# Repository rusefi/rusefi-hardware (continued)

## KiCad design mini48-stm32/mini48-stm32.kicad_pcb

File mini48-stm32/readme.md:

Brain board stm lqfp48 pin

* TC2030
* CANbus

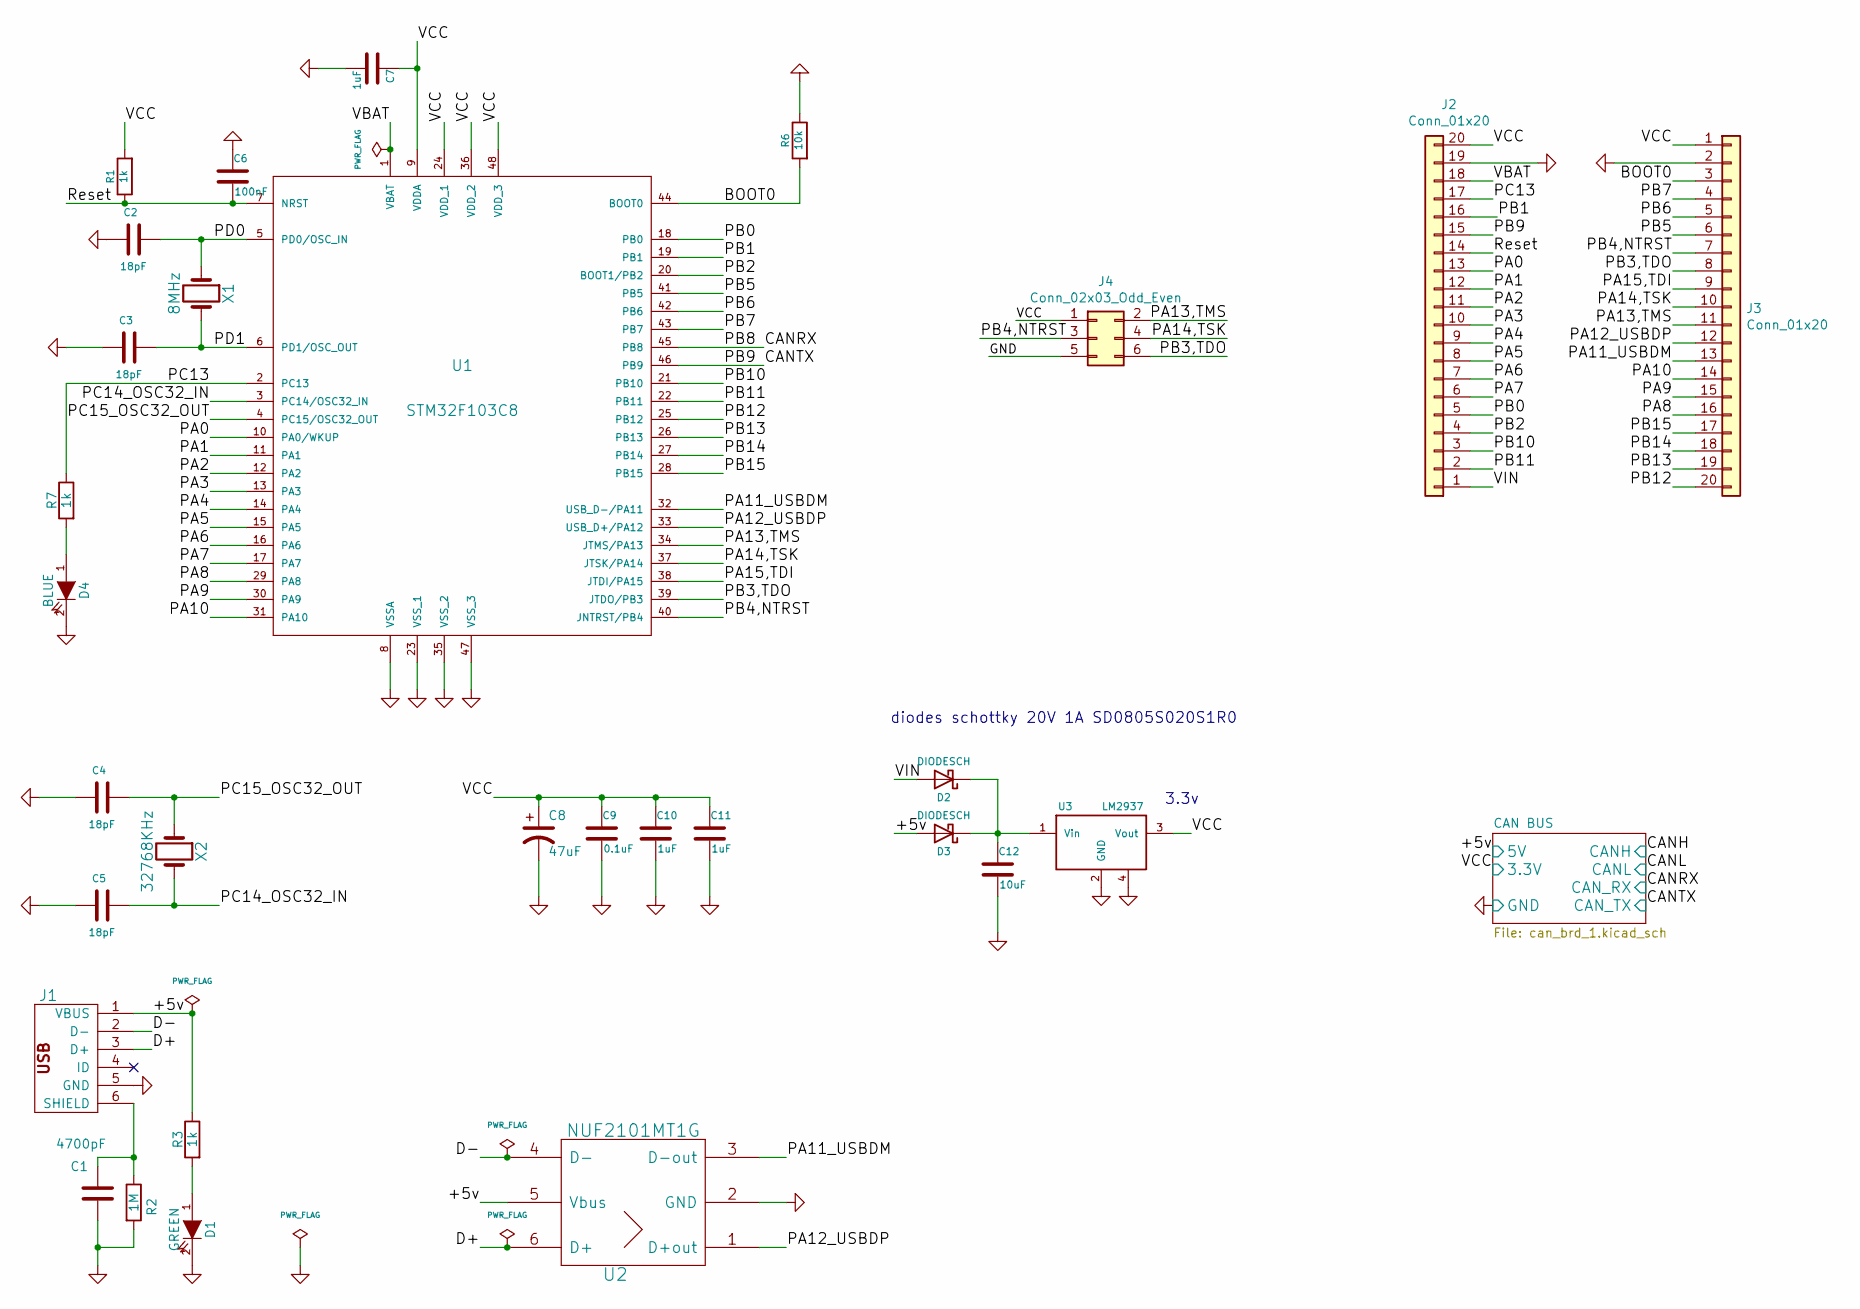
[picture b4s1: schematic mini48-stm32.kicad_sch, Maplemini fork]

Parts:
C1: 4700pF; C_0805_2012Metric; MPN 0805B472K500CT; JLC PN C123621
C2, C3, C4, C5: 18pF; C_0805_2012Metric; MPN CC0805JRNPO9BN180; JLC PN C113825
C6: 100nF; C_0805_2012Metric; MPN CC0805JRX7R9BB104; JLC PN C111492
C7, C10, C11: 1uF; C_0805_2012Metric; MPN CC0805ZKY5V9BB105; JLC PN C106838
C8: 47uF; CP_Elec_4x5.3; MPN GRM21BR61A476ME15L; JLC PN C124129
C9: 0.1uF; C_0805_2012Metric; MPN CC0805JRX7R9BB104; JLC PN C111492
C12: 10uF; C_0805_2012Metric; MPN GRM21BR71A106KA73L; JLC PN C117956
D1: GREEN; LED-0805_A; MPN C693904; JLC PN MHS171UGCT
D2, D3: DIODESCH; D_0805_2012Metric
D4: BLUE; LED-0805_A; MPN C99870; JLC PN 17-21/BHC-AP1Q2/3T
J1: MINI-USB; MINI-USB-5P-3400020P1
J2, J3: Conn_01x20; PIN_ARRAY_20X1
J4: Conn_02x03_Odd_Even; Tag-Connect_TC2030-IDC-NL_2x03_P1.27mm_Vertical
R1, R3, R7: 1k; R_0805_2012Metric; MPN ARG05FTC1001; JLC PN C218388
R2: 1M; R_0805_2012Metric; MPN ERJ6GEYJ105V; JLC PN C230655
R6: 10k; R_0805_2012Metric; MPN RMS10FT1002; JLC PN C212284
U1: STM32F103C8; LQFP-48_7x7mm_P0.5mm; MPN STM32F103C8T6
U2: NUF2101MT1G; SOT-23-6; MPN USBLC6-2SC6; JLC PN C2827654
U3: LM2937; SOT-223; MPN LM2937IMP-3.3/NOPB; JLC PN C140265
X1: 8MHz; HC-49V
X2: 32768KHz; MC-306

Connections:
/+5v: D3.2 (A), J1.1 (VBUS), R3.1, U2.5 (Vbus); also elsewhere on the board
/BOOT0: J3.3, R6.2, U1.44 (BOOT0)
/CANRX: U1.45 (PB8); also elsewhere on the board
/CANTX: J2.15, U1.46 (PB9); also elsewhere on the board
/D+: J1.3 (D+), U2.6 (D+)
/D-: J1.2 (D-), U2.4 (D-)
/PA0: J2.13, U1.10 (PA0/WKUP)
/PA1: J2.12, U1.11 (PA1)
/PA2: J2.11, U1.12 (PA2)
/PA3: J2.10, U1.13 (PA3)
/PA4: J2.9, U1.14 (PA4)
/PA5: J2.8, U1.15 (PA5)
/PA6: J2.7, U1.16 (PA6)
/PA7: J2.6, U1.17 (PA7)
/PA8: J3.16, U1.29 (PA8)
/PA9: J3.15, U1.30 (PA9)
/PA10: J3.14, U1.31 (PA10)
/PA11_USBDM: J3.13, U1.32 (USB_D-/PA11), U2.3 (D-out)
/PA12_USBDP: J3.12, U1.33 (USB_D+/PA12), U2.1 (D+out)
/PA13,TMS: J3.11, J4.2, U1.34 (JTMS/PA13)
/PA14,TSK: J3.10, J4.4, U1.37 (JTSK/PA14)
/PA15,TDI: J3.9, U1.38 (JTDI/PA15)
/PB0: J2.5, U1.18 (PB0)
/PB1: J2.16, U1.19 (PB1)
/PB2: J2.4, U1.20 (BOOT1/PB2)
/PB3,TDO: J3.8, J4.6, U1.39 (JTDO/PB3)
/PB4,NTRST: J3.7, J4.3, U1.40 (JNTRST/PB4)
/PB5: J3.6, U1.41 (PB5)
/PB6: J3.5, U1.42 (PB6)
/PB7: J3.4, U1.43 (PB7)
/PB10: J2.3, U1.21 (PB10)
/PB11: J2.2, U1.22 (PB11)
/PB12: J3.20, U1.25 (PB12)
/PB13: J3.19, U1.26 (PB13)
/PB14: J3.18, U1.27 (PB14)
/PB15: J3.17, U1.28 (PB15)
/PC13: J2.17, R7.1, U1.2 (PC13)
/PC14_OSC32_IN: C5.2, U1.3 (PC14/OSC32_IN), X2.2
/PC15_OSC32_OUT: C4.2, U1.4 (PC15/OSC32_OUT), X2.1
/PD0: C2.2, U1.5 (PD0/OSC_IN), X1.1
/PD1: C3.2, U1.6 (PD1/OSC_OUT), X1.2
/Reset: C6.2, J2.14, R1.1, U1.7 (NRST)
/VBAT: J2.18, U1.1 (VBAT)
/VCC: C7.1, C8.1, C9.1, C10.1, C11.1, J2.20, J3.1, J4.1, R1.2, U1.9 (VDDA), U1.24 (VDD_1), U1.36 (VDD_2), U1.48 (VDD_3), U3.3 (Vout); also elsewhere on the board
/VIN: D2.2 (A), J2.1
GND: C1.1, C2.1, C3.1, C4.1, C5.1, C6.1, C7.2, C8.2, C9.2, C10.2, C11.2, C12.2, D1.2 (K), D4.2 (K), J1.5 (GND), J2.19, J3.2, J4.5, R2.2, R6.1, U1.8 (VSSA), U1.23 (VSS_1), U1.35 (VSS_2), U1.47 (VSS_3), U2.2 (GND), U3.2 (GND), U3.4; also elsewhere on the board
unnamed: C1.2, J1.6 (SHIELD), R2.1
unnamed: C12.1, D2.1 (K), D3.1 (K), U3.1 (Vin)
unnamed: D1.1 (A), R3.2
unnamed: D4.1 (A), R7.2

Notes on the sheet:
diodes schottky 20V 1A SD0805S020S1R0
3.3v

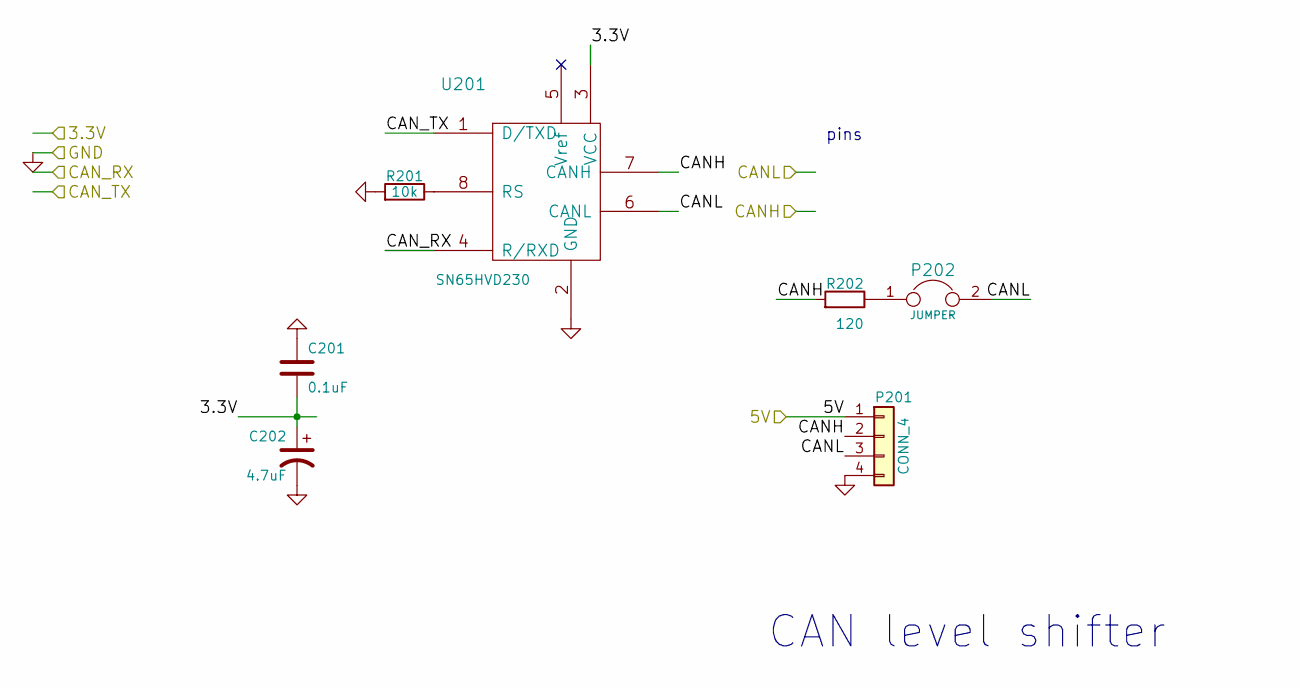
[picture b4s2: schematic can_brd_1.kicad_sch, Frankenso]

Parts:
C201: 0.1uF; C_0805_2012Metric; MPN CC0805JRX7R9BB104; JLC PN C111492
C202: 4.7uF; C_0805_2012Metric; MPN 0805B472K500CT; JLC PN C123621
P201: CONN_4; SIL-4
P202: JUMPER; JUMPER-2
R201: 10k; R_0805_2012Metric; MPN RMS10FT1002; JLC PN C212284
R202: 120; R_0805_2012Metric; MPN CRH0805J120RP05Z; JLC PN C149652
U201: SN65HVD230; SO-8_3.9x4.9mm_P1.27mm; MPN SN65HVD230DR; JLC PN C12084

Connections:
/+5v: P201.1; also elsewhere on the board
/CANH: P201.2, R202.2, U201.7 (CANH)
/CANL: P201.3, P202.2, U201.6 (CANL)
/CANRX: U201.4 (R/RXD); also elsewhere on the board
/CANTX: U201.1 (D/TXD); also elsewhere on the board
/VCC: C201.2, C202.1, U201.3 (VCC); also elsewhere on the board
GND: C201.1, C202.2, P201.4, R201.2, U201.2 (GND); also elsewhere on the board
unnamed: P202.1, R202.1
unnamed: R201.1, U201.8 (RS)

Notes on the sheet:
CAN level shifter
pins

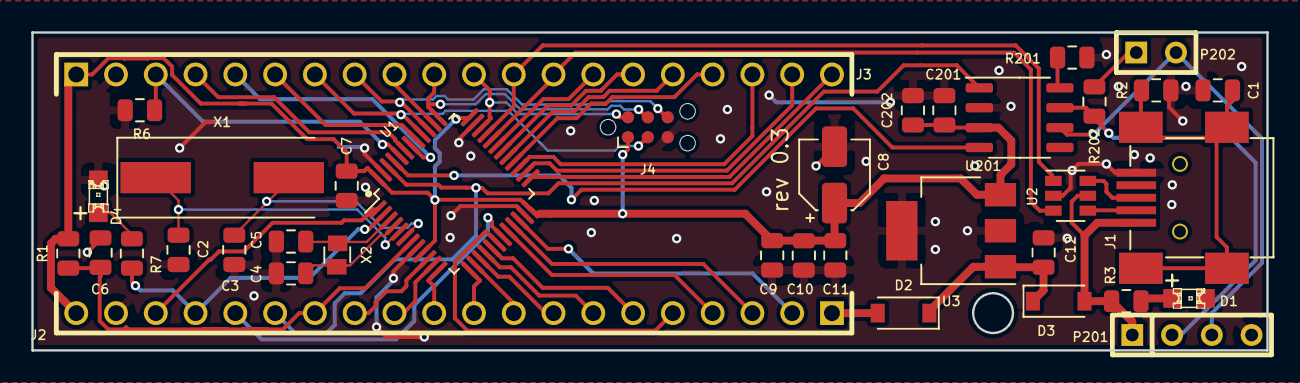
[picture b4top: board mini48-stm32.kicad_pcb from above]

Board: 2 copper layers, 78.9 x 20.3 mm, 37 parts (0 on the bottom side), 54 nets.

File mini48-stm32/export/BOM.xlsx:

Comment | Designator | Footprint | JLCPCB Part #
4700pF | C1 | Capacitor_SMD:C_0805_2012Metric | C123621
18pF | C2 | Capacitor_SMD:C_0805_2012Metric | C113825
18pF | C3 | Capacitor_SMD:C_0805_2012Metric | C113825
12pF | C4 | Capacitor_SMD:C_0805_2012Metric | C0805
12pF | C5 | Capacitor_SMD:C_0805_2012Metric | C0805
100nF | C6 | Capacitor_SMD:C_0805_2012Metric | C111492
1uF | C7 | Capacitor_SMD:C_0805_2012Metric | C106838
47uF | C8 | Capacitor_SMD:CP_Elec_4x5.3 | C124129
0.1uF | C9 | Capacitor_SMD:C_0805_2012Metric | C111492
1uF | C10 | Capacitor_SMD:C_0805_2012Metric | C106838
1uF | C11 | Capacitor_SMD:C_0805_2012Metric | C106838
10uF | C12 | Capacitor_SMD:C_0805_2012Metric | C117956
0.1uF | C201 | Capacitor_SMD:C_0805_2012Metric | C111492
4.7uF | C202 | Capacitor_SMD:C_0805_2012Metric | C123621
GREEN | D1 | LED-0805_A | C693904
DIODESCH | D2 | Diode_SMD:D_SOD-123 | C82288
DIODESCH | D3 | Diode_SMD:D_SOD-123 | C82288
BLUE | D4 | LED-0805_A | C99870
MINI-USB | J1 | MINI-USB-5P-3400020P1 | C2681563
Conn_01x20 | J2 | mini48-stm32:PIN_ARRAY_20X1 | DNP
Conn_01x20 | J3 | mini48-stm32:PIN_ARRAY_20X1 | DNP
Conn_02x03_Odd_Even | J4 | Connector:Tag-Connect_TC2030-IDC-NL_2x03_P1.27mm_Vertical | DNP
CONN_4 | P201 | SIL-4 | DNP
JUMPER | P202 | JUMPER-2 | DNP
1k | R1 | Resistor_SMD:R_0805_2012Metric | C218388
1M | R2 | Resistor_SMD:R_0805_2012Metric | C230655
1k | R3 | Resistor_SMD:R_0805_2012Metric | C218388
10k | R6 | Resistor_SMD:R_0805_2012Metric | C212284
1k | R7 | Resistor_SMD:R_0805_2012Metric | C218388
10k | R201 | Resistor_SMD:R_0805_2012Metric | C212284
120 | R202 | Resistor_SMD:R_0805_2012Metric | C149652
STM32F103C8 | U1 | Package_QFP:LQFP-48_7x7mm_P0.5mm | C8734
NUF2101MT1G | U2 | Package_TO_SOT_SMD:SOT-23-6 | C2827654
LM2937 | U3 | Package_TO_SOT_SMD:SOT-223 | C140265
SN65HVD230 | U201 | Package_SO:SO-8_3.9x4.9mm_P1.27mm | C12084
8MHz | X1 | Crystal:Crystal_SMD_HC49-SD | C106809
32.768KHz | X2 | mini48-stm32:SMD2012-2P | C515343

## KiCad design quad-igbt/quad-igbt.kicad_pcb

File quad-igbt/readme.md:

x4 coil driver

For instance ISL9V3040S3S

See also https://github.com/rusefi/rusefi/tree/master/hardware/DDPAK_breakout

https://www.youtube.com/watch?v=TUJzp6ig_bQ

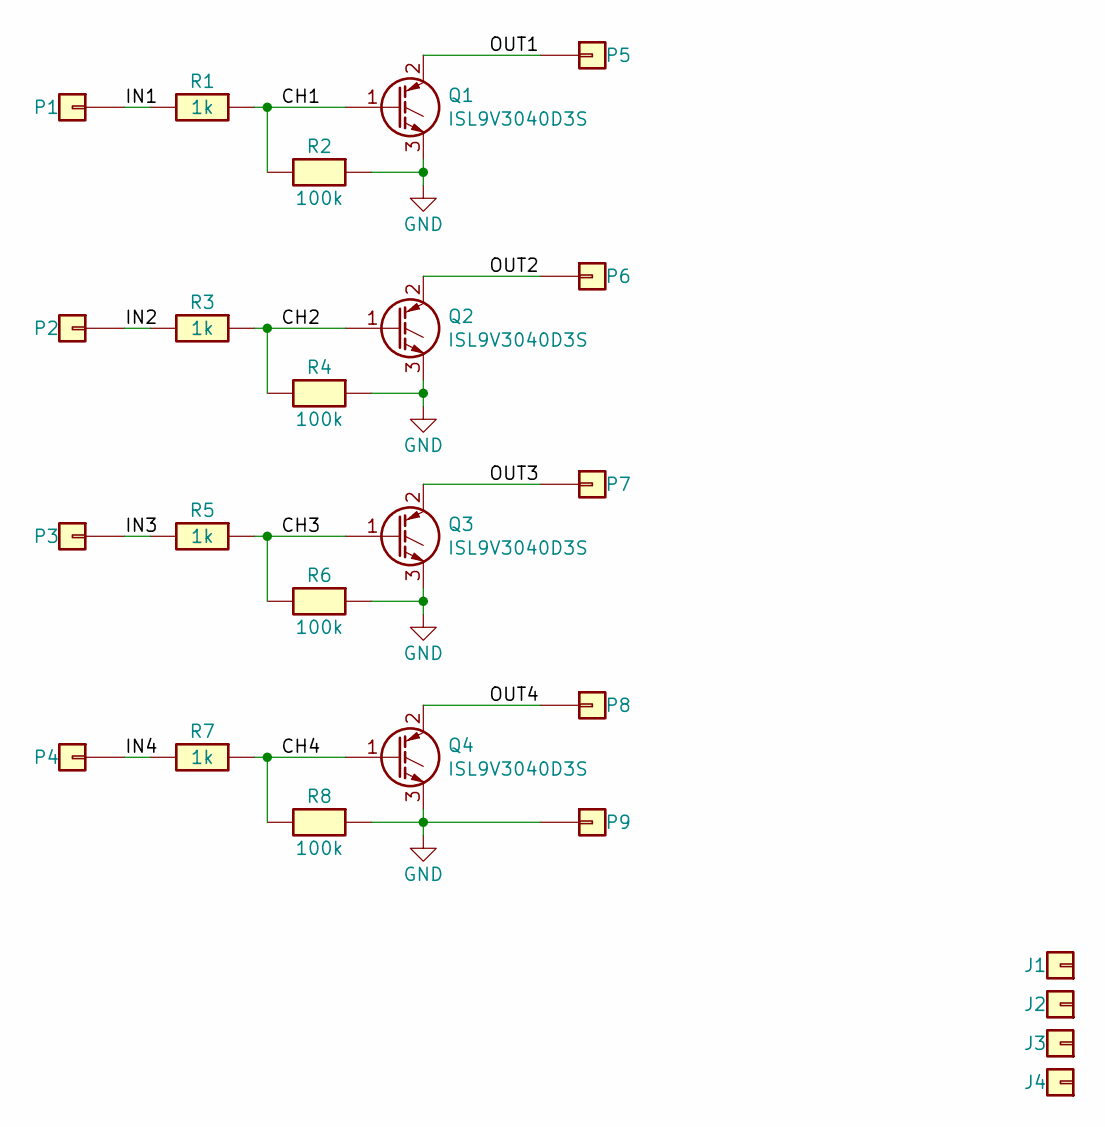
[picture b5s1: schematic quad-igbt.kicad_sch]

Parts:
J1, J2, J3, J4: Conn_01x01; MountingHole_5mm
P1, P2, P3, P4, P5, P6, P7, P8, P9: Pad; PAD-TH
Q1, Q2, Q3, Q4: ISL9V3040D3S; TO-263-2; LCSC C462128
R1, R3, R5, R7: 1k; R0805; LCSC C17513
R2, R4, R6, R8: 100k; R0805; LCSC C149504

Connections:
/CH1: Q1.1 (G), R1.1, R2.2
/CH2: Q2.1 (G), R3.1, R4.2
/CH3: Q3.1 (G), R5.1, R6.2
/CH4: Q4.1 (G), R7.1, R8.2
/IN1: P1.1, R1.2
/IN2: P2.1, R3.2
/IN3: P3.1, R5.2
/IN4: P4.1, R7.2
/OUT1: P5.1, Q1.2 (C)
/OUT2: P6.1, Q2.2 (C)
/OUT3: P7.1, Q3.2 (C)
/OUT4: P8.1, Q4.2 (C)
GND: P9.1, Q1.3 (E), Q2.3 (E), Q3.3 (E), Q4.3 (E), R2.1, R4.1, R6.1, R8.1

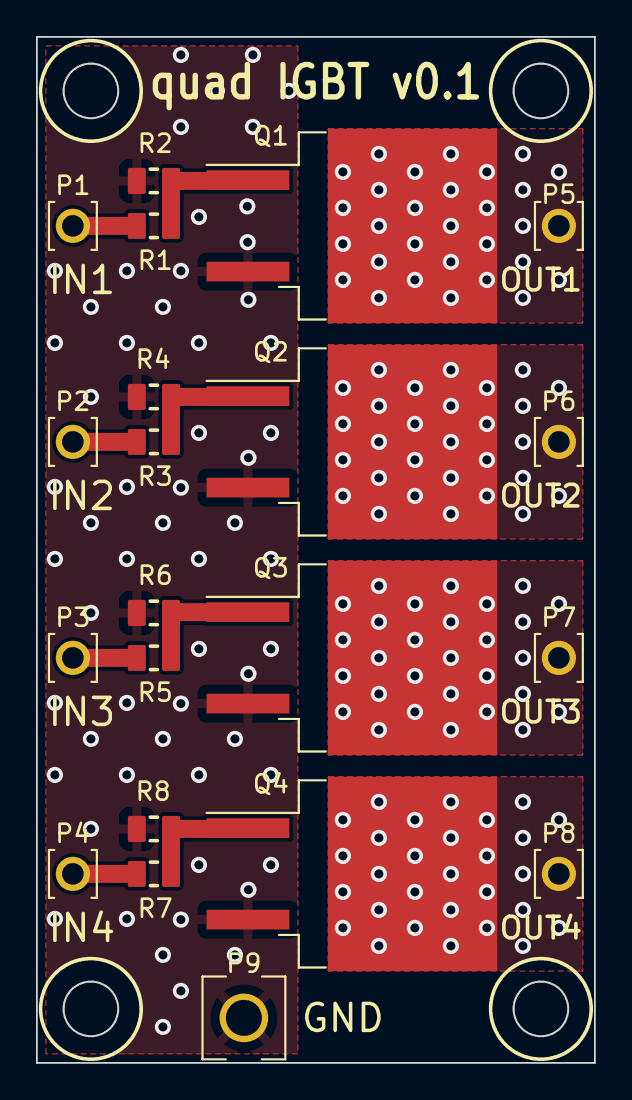
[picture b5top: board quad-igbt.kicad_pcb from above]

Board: 2 copper layers, 31.0 x 57.0 mm, 25 parts (0 on the bottom side), 13 nets.

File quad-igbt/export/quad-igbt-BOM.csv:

Comment,Designator,Footprint,LCSC Part #
"Pad","P1","hellen-one-common:PAD-TH",""
"Pad","P2","hellen-one-common:PAD-TH",""
"Pad","P3","hellen-one-common:PAD-TH",""
"Pad","P4","hellen-one-common:PAD-TH",""
"Pad","P5","hellen-one-common:PAD-TH",""
"Pad","P6","hellen-one-common:PAD-TH",""
"Pad","P7","hellen-one-common:PAD-TH",""
"Pad","P8","hellen-one-common:PAD-TH",""
"Pad","P9","hellen-one-common:PAD-TH",""
"ISL9V3040D3S","Q1","Package_TO_SOT_SMD:TO-263-2","C462128"
"ISL9V3040D3S","Q2","Package_TO_SOT_SMD:TO-263-2","C462128"
"ISL9V3040D3S","Q3","Package_TO_SOT_SMD:TO-263-2","C462128"
"ISL9V3040D3S","Q4","Package_TO_SOT_SMD:TO-263-2","C462128"
"1k","R1","hellen-one-common:R0805","C17513"
"100k","R2","hellen-one-common:R0805","C149504"
"1k","R3","hellen-one-common:R0805","C17513"
"100k","R4","hellen-one-common:R0805","C149504"
"1k","R5","hellen-one-common:R0805","C17513"
"100k","R6","hellen-one-common:R0805","C149504"
"1k","R7","hellen-one-common:R0805","C17513"
"100k","R8","hellen-one-common:R0805","C149504"

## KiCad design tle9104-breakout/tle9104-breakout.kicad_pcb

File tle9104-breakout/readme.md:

See https://github.com/mck1117/tle9104-breakout

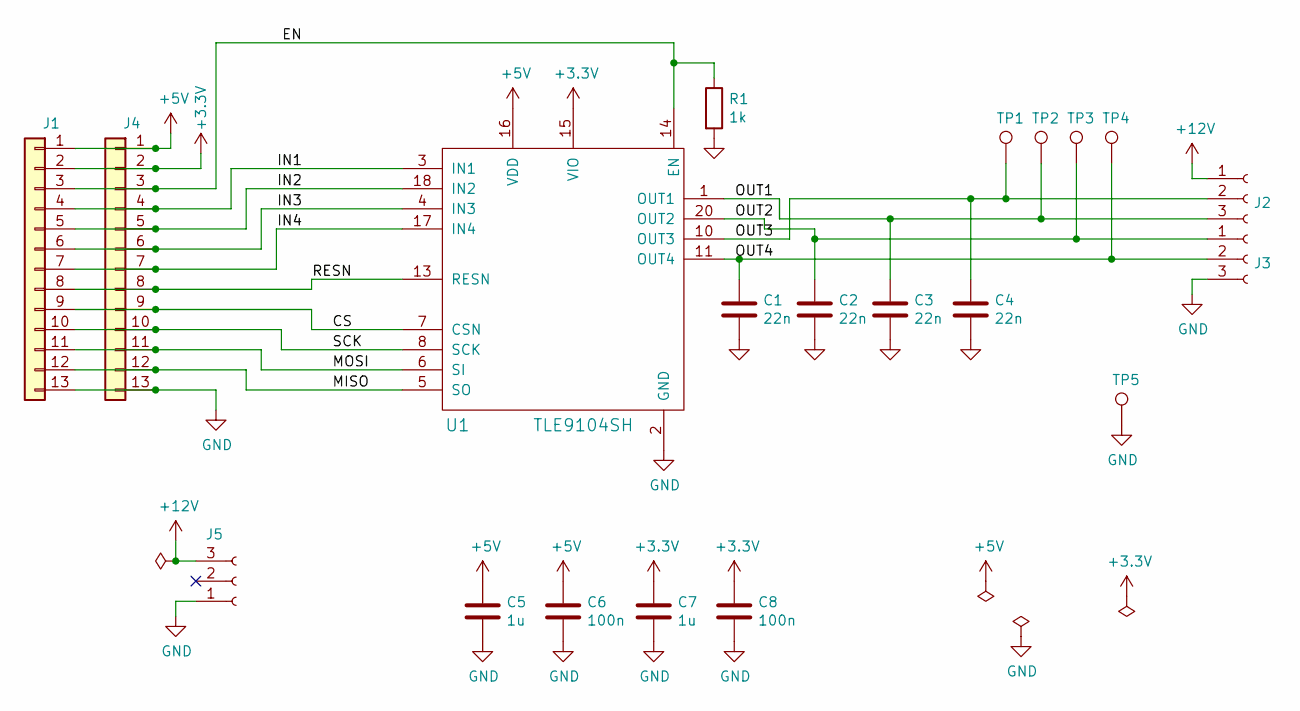
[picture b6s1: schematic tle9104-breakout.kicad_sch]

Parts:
C1, C2, C3, C4: 22n; C_0603_1608Metric; LCSC C21122
C5, C7: 1u; C_0603_1608Metric; LCSC C15849
C6, C8: 100n; C_0402_1005Metric; LCSC C307331
J1, J4: Conn_01x13; PinHeader_1x13_P2.54mm_Vertical
J2, J3: Conn_01x03_Female; PhoenixContact_MCV_1,5_3-G-5.08_1x03_P5.08mm_Vertical
J5: Conn_01x03_Female; PhoenixContact_MSTBVA_2,5_3-G_1x03_P5.00mm_Vertical
R1: 1k; R_0603_1608Metric; LCSC C21190
TP1, TP2, TP3, TP4, TP5: TestPoint; TestPoint_Loop_D2.50mm_Drill1.0mm
U1: TLE9104SH; PG-DSO-20-88; LCSC C2650386

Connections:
+3V3: C7.1, C8.1, J1.2, J4.2, U1.15 (VIO)
+5V: C5.1, C6.1, J1.1, J4.1, U1.16 (VDD)
+12V: J2.1, J5.3
/CS: J1.9, J4.9, U1.7 (CSN)
/EN: J1.3, J4.3, R1.1, U1.14 (EN)
/IN1: J1.4, J4.4, U1.3 (IN1)
/IN2: J1.5, J4.5, U1.18 (IN2)
/IN3: J1.6, J4.6, U1.4 (IN3)
/IN4: J1.7, J4.7, U1.17 (IN4)
/MISO: J1.12, J4.12, U1.5 (SO)
/MOSI: J1.11, J4.11, U1.6 (SI)
/OUT1: C3.1, J2.3, TP2.1, U1.1 (OUT1)
/OUT2: C2.1, J3.1, TP3.1, U1.20 (OUT2)
/OUT3: C4.1, J2.2, TP1.1, U1.10 (OUT3)
/OUT4: C1.1, J3.2, TP4.1, U1.11 (OUT4)
/RESN: J1.8, J4.8, U1.13 (RESN)
/SCK: J1.10, J4.10, U1.8 (SCK)
GND: C1.2, C2.2, C3.2, C4.2, C5.2, C6.2, C7.2, C8.2, J1.13, J3.3, J4.13, J5.1, R1.2, TP5.1, U1.2 (GND), U1.9 (GND), U1.12 (GND), U1.19 (GND), U1.21 (GND)

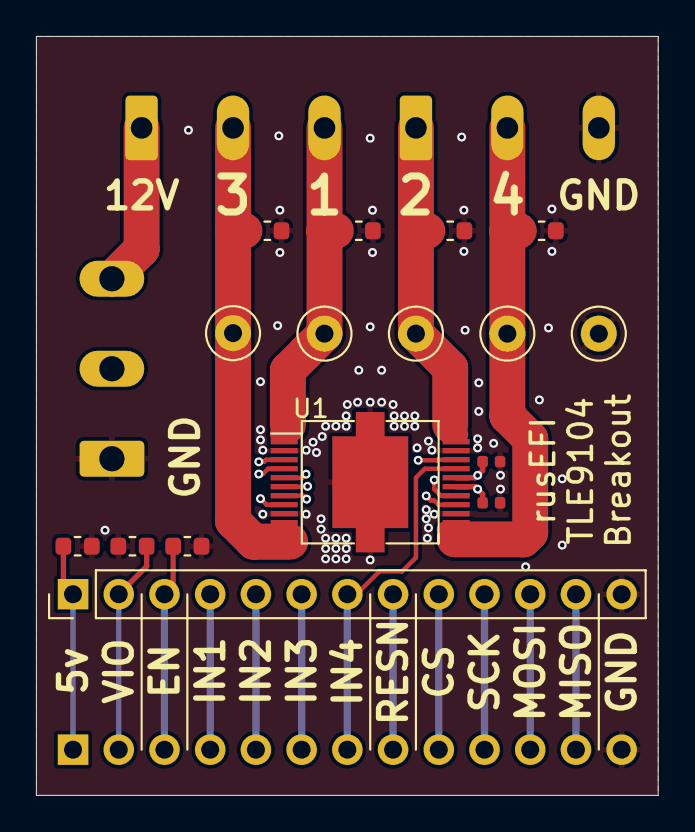
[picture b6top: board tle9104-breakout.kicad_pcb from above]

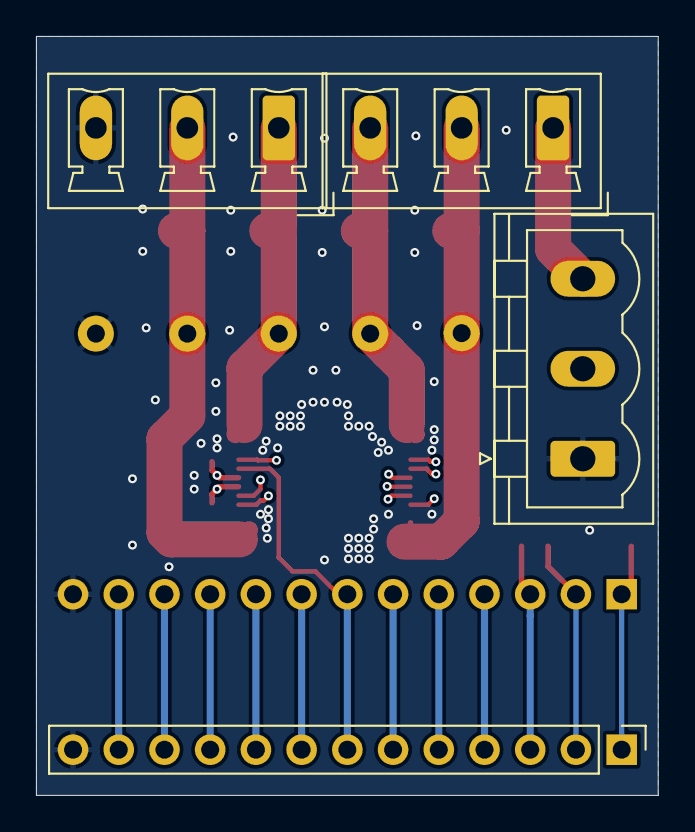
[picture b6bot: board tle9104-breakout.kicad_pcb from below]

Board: 4 copper layers, 34.5 x 42.2 mm, 20 parts (4 on the bottom side), 18 nets.

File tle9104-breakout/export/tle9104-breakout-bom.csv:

"Comment","Designator","Footprint","LCSC Part #"
"22n","C1","Capacitor_SMD:C_0603_1608Metric","C21122"
"22n","C2","Capacitor_SMD:C_0603_1608Metric","C21122"
"22n","C3","Capacitor_SMD:C_0603_1608Metric","C21122"
"22n","C4","Capacitor_SMD:C_0603_1608Metric","C21122"
"1u","C5","Capacitor_SMD:C_0603_1608Metric","C15849"
"100n","C6","Capacitor_SMD:C_0402_1005Metric","C307331"
"1u","C7","Capacitor_SMD:C_0603_1608Metric","C15849"
"100n","C8","Capacitor_SMD:C_0402_1005Metric","C307331"
"Conn_01x13","J1","Connector_PinHeader_2.54mm:PinHeader_1x13_P2.54mm_Vertical",""
"Conn_01x03_Female","J2","Connector_Phoenix_MC_HighVoltage:PhoenixContact_MCV_1,5_3-G-5.08_1x03_P5.08mm_Vertical",""
"Conn_01x03_Female","J3","Connector_Phoenix_MC_HighVoltage:PhoenixContact_MCV_1,5_3-G-5.08_1x03_P5.08mm_Vertical",""
"Conn_01x13","J4","Connector_PinHeader_2.54mm:PinHeader_1x13_P2.54mm_Vertical",""
"Conn_01x03_Female","J5","Connector_Phoenix_MSTB:PhoenixContact_MSTBVA_2,5_3-G_1x03_P5.00mm_Vertical",""
"1k","R1","Resistor_SMD:R_0603_1608Metric","C21190"
"TestPoint","TP1","TestPoint:TestPoint_Loop_D2.50mm_Drill1.0mm",""
"TestPoint","TP2","TestPoint:TestPoint_Loop_D2.50mm_Drill1.0mm",""
"TestPoint","TP3","TestPoint:TestPoint_Loop_D2.50mm_Drill1.0mm",""
"TestPoint","TP4","TestPoint:TestPoint_Loop_D2.50mm_Drill1.0mm",""
"TestPoint","TP5","TestPoint:TestPoint_Loop_D2.50mm_Drill1.0mm",""
"TLE9104SH","U1","rusefi:PG-DSO-20-88","C2650386"
